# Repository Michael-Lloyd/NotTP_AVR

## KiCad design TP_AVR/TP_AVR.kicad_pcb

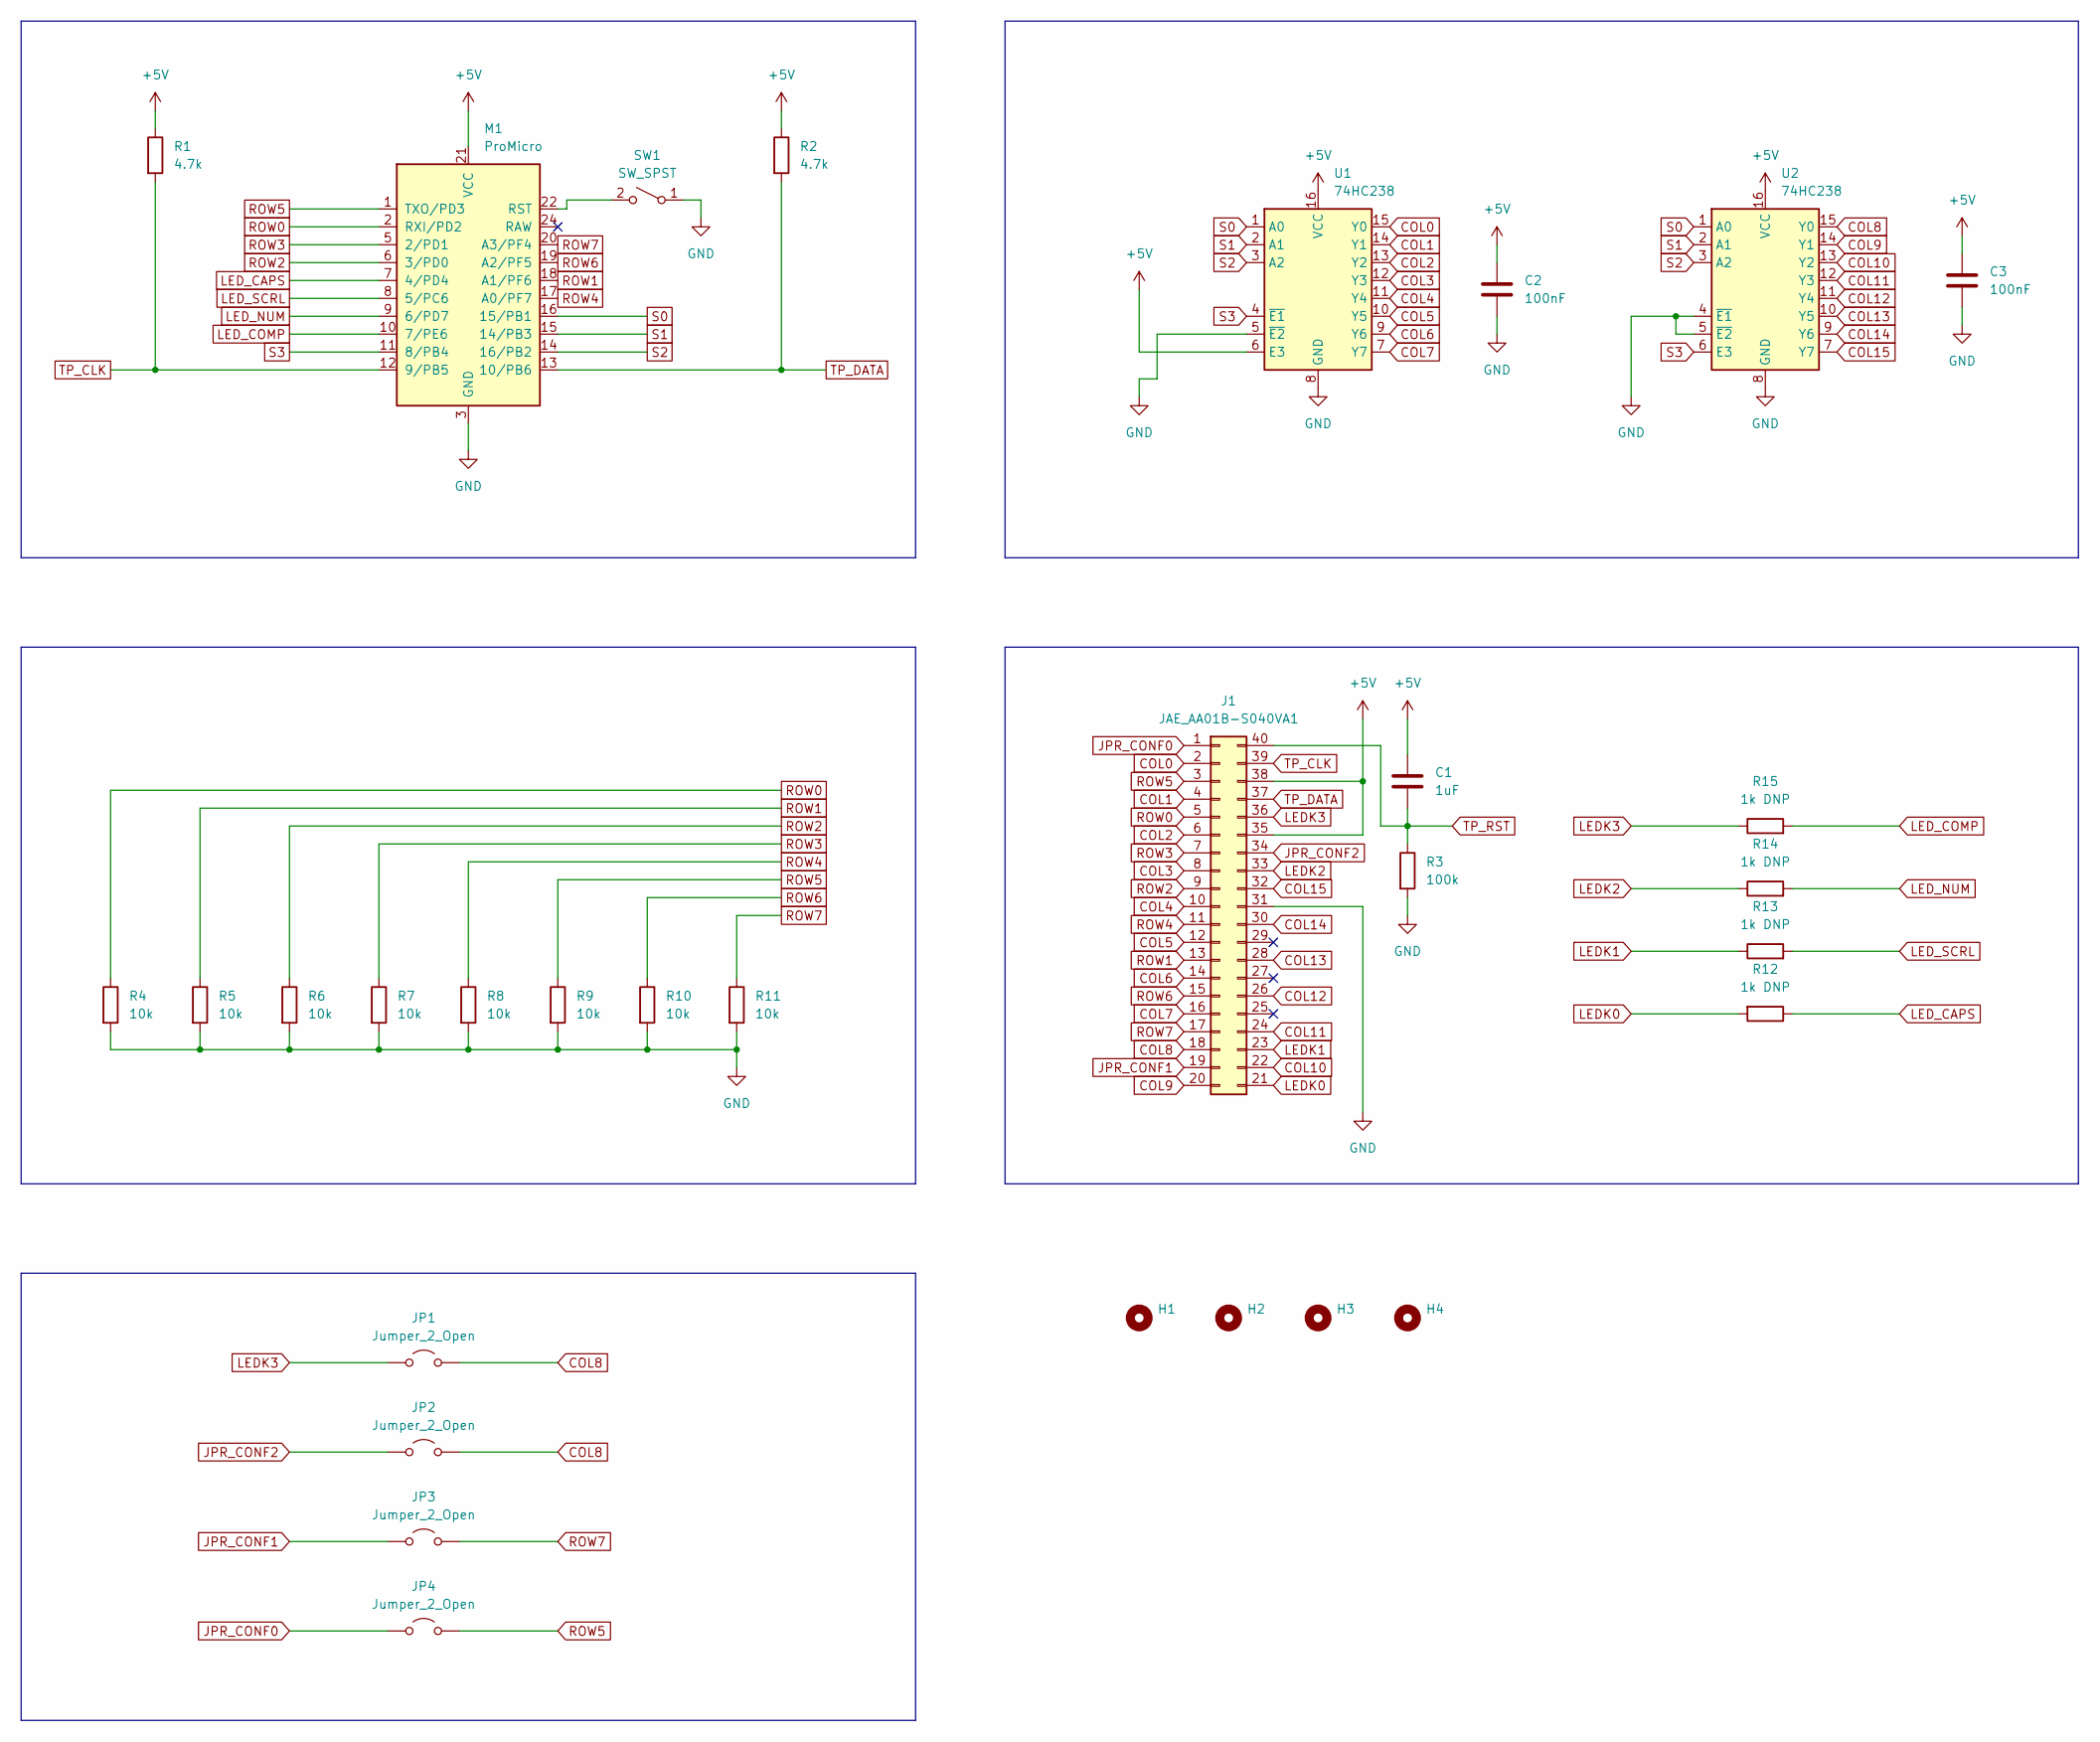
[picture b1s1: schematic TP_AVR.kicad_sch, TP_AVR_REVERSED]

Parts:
C1: 1uF; C_0603_1608Metric
C2, C3: 100nF; C_0603_1608Metric
H1, H2, H3, H4: MountingHole; MountingHole_2.2mm_M2
J1: JAE_AA01B-S040VA1
JP1, JP2, JP3, JP4: Jumper_2_Open; SolderJumper-2_P1.3mm_Open_Pad1.0x1.5mm
M1: ProMicro
R1, R2: 4.7k; R_0603_1608Metric
R3: 100k; R_0603_1608Metric
R4, R5, R6, R7, R8, R9, R10, R11: 10k; R_0603_1608Metric
R12, R13, R14, R15: 1k DNP; R_0603_1608Metric
SW1: SW_SPST; SW_SPST_Omron_B3F-315x_Angled
U1, U2: 74HC238; TSSOP-16_4.4x5mm_P0.65mm

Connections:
+5V: C1.1, C2.1, C3.1, J1.35, J1.38, M1.21 (VCC), R1.1, R2.1, U1.6 (E3), U1.16 (VCC), U2.16 (VCC)
COL0: J1.2, U1.15 (Y0)
COL1: J1.4, U1.14 (Y1)
COL2: J1.6, U1.13 (Y2)
COL3: J1.8, U1.12 (Y3)
COL4: J1.10, U1.11 (Y4)
COL5: J1.12, U1.10 (Y5)
COL6: J1.14, U1.9 (Y6)
COL7: J1.16, U1.7 (Y7)
COL8: J1.18, JP1.2 (B), JP2.2 (B), U2.15 (Y0)
COL9: J1.20, U2.14 (Y1)
COL10: J1.22, U2.13 (Y2)
COL11: J1.24, U2.12 (Y3)
COL12: J1.26, U2.11 (Y4)
COL13: J1.28, U2.10 (Y5)
COL14: J1.30, U2.9 (Y6)
COL15: J1.32, U2.7 (Y7)
GND: C2.2, C3.2, J1.31, M1.3 (GND), M1.4 (GND), M1.23 (GND), R3.2, R4.2, R5.2, R6.2, R7.2, R8.2, R9.2, R10.2, R11.2, SW1.1 (A), U1.5 (~E2), U1.8 (GND), U2.4 (~E1), U2.5 (~E2), U2.8 (GND)
JPR_CONF0: J1.1, JP4.1 (A)
JPR_CONF1: J1.19, JP3.1 (A)
JPR_CONF2: J1.34, JP2.1 (A)
LEDK0: J1.21, R12.2
LEDK1: J1.23, R13.1
LEDK2: J1.33, R14.1
LEDK3: J1.36, JP1.1 (A), R15.1
LED_CAPS: M1.7 (4/PD4), R12.1
LED_COMP: M1.10 (7/PE6), R15.2
LED_NUM: M1.9 (6/PD7), R14.2
LED_SCRL: M1.8 (5/PC6), R13.2
unnamed: M1.22 (RST), SW1.2 (B)
ROW0: J1.5, M1.2 (RXI/PD2), R4.1
ROW1: J1.13, M1.18 (A1/PF6), R5.1
ROW2: J1.9, M1.6 (3/PD0), R6.1
ROW3: J1.7, M1.5 (2/PD1), R7.1
ROW4: J1.11, M1.17 (A0/PF7), R8.1
ROW5: J1.3, JP4.2 (B), M1.1 (TXO/PD3), R9.1
ROW6: J1.15, M1.19 (A2/PF5), R10.1
ROW7: J1.17, JP3.2 (B), M1.20 (A3/PF4), R11.1
S0: M1.16 (15/PB1), U1.1 (A0), U2.1 (A0)
S1: M1.15 (14/PB3), U1.2 (A1), U2.2 (A1)
S2: M1.14 (16/PB2), U1.3 (A2), U2.3 (A2)
S3: M1.11 (8/PB4), U1.4 (~E1), U2.6 (E3)
TP_CLK: J1.39, M1.12 (9/PB5), R1.2
TP_DATA: J1.37, M1.13 (10/PB6), R2.2
TP_RST: C1.2, J1.40, R3.1

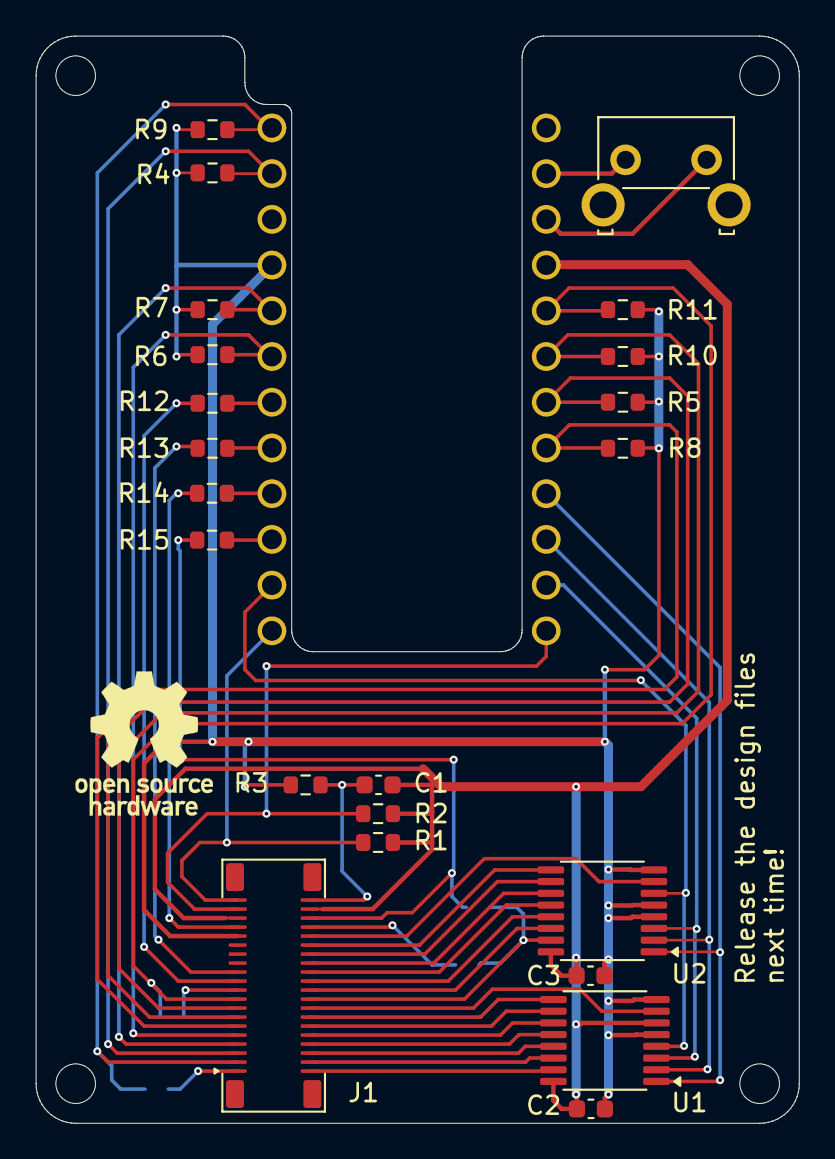
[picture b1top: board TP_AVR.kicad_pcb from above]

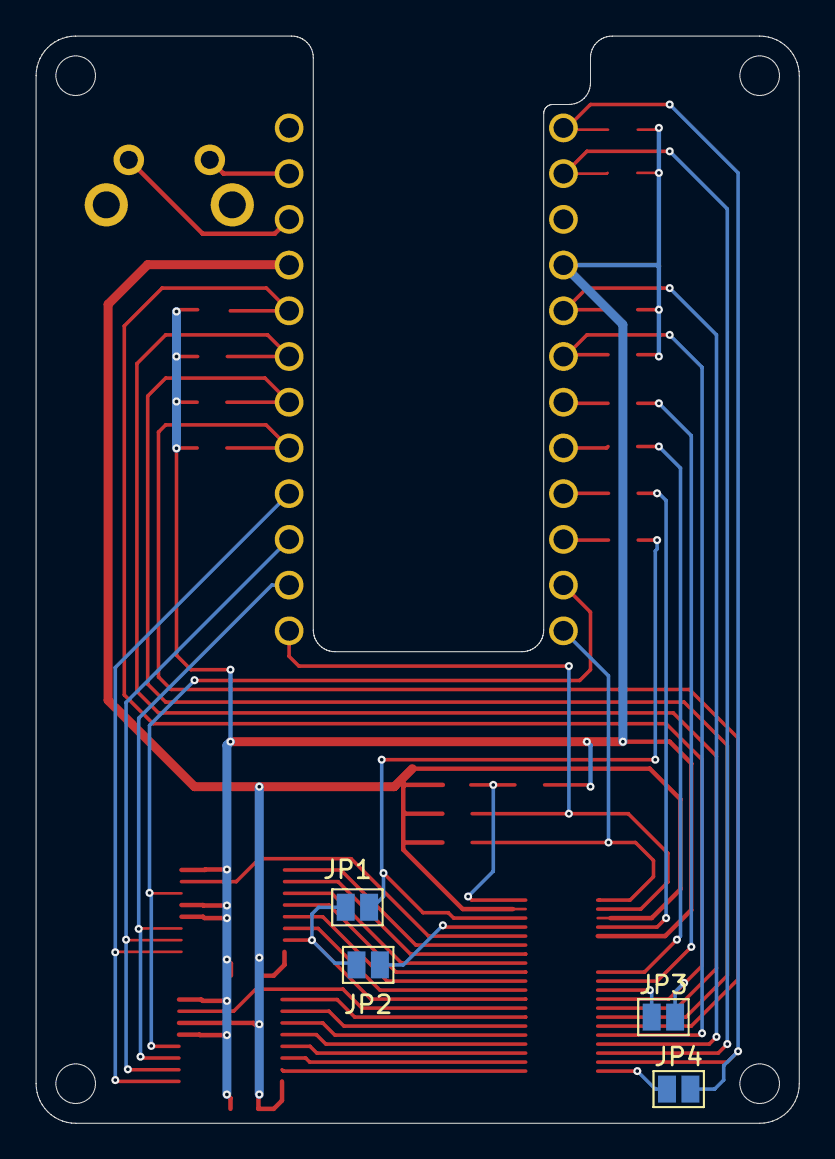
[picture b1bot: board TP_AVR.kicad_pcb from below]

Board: 2 copper layers, 42.4 x 60.4 mm, 31 parts (4 on the bottom side), 45 nets.

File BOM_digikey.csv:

Quantity,Manufacturer Part Number,Manufacturer,Description,Customer Reference,Notes
2,RC0603FR-074K7L,Yageo,RES 4.7K OHM 1% 1/10W 0603,"R1,R2",PS/2 pull-ups on TP_CLK / TP_DATA
1,RC0603FR-07100KL,Yageo,RES 100K OHM 1% 1/10W 0603,R3,TrackPoint power-on reset RC (with C1)
8,RC0603FR-0710KL,Yageo,RES 10K OHM 1% 1/10W 0603,"R4,R5,R6,R7,R8,R9,R10,R11",Matrix row pulldowns (required with 74HC238)
4,RC0603FR-071KL,Yageo,RES 1K OHM 1% 1/10W 0603,"R12,R13,R14,R15",LED current limit - fit only for X220/X230; adjust 1k-2k per LED colour
1,CL10A105KA8NNNC,Samsung Electro-Mechanics,CAP CER 1UF 25V X5R 0603,C1,TrackPoint reset RC (+5V to TP_RST)
2,CL10B104KB8NNNC,Samsung Electro-Mechanics,CAP CER 0.1UF 50V X7R 0603,"C2,C3",Decoupling for U1 / U2
2,"74HC238PW,118",Nexperia,IC DECODER/DEMUX 1X3:8 TSSOP-16,"U1,U2",Two used as a 4-to-16 column driver. Alt: TI SN74HC238PWR
1,DEV-12640,SparkFun Electronics,Pro Micro 5V/16MHz ATmega32U4 board,M1,Any Pro Micro compatible (5V/16MHz) works
1,B3F-3152,Omron Electronics,SWITCH TACTILE SPST-NO RIGHT ANGLE,SW1,Reset (RST to GND) - optional; any B3F-315x variant (stem height differs)
1,AA01B-S040VA1-R3000,JAE Electronics,CONN KEYBOARD 40P 0.5MM PITCH SMD,J1,OBSOLETE - not stocked by DigiKey. See notes below.
